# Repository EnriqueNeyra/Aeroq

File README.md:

# Aeroq

> [!IMPORTANT]
> **Aeroq is no longer maintained. Its successor is [Aether](https://github.com/EnriqueNeyra/aether).**
>
> Aether is the new version of this project. It uses a Sensirion SEN66 sensor (adding NOx), runs ESPHome firmware with Home Assistant integration, and adds a local web dashboard, OTA updates, and a browser-based USB flasher. For a new build, use Aether.
>
> This repository is kept as a reference for existing Aeroq v3 builds and will not receive further updates.

### A comprehensive indoor air quality monitor, capturing Temperature, Relative Humidity, CO2 (ppm), VOC (Index), and PM 1.0, 2.5, 4.0, 10 (ug/m3)

## Contents
- [Project Overview](#project-overview)
- [Required Hardware](#required-hardware)
- [Firmware Setup](#firmware-setup)
- [Assembly](#assembly)
- [Using Aeroq](#using-aeroq)
- [Troubleshooting](#troubleshooting)

---
## Project Overview

### Hardware
Schematic and PCB designed using KiCad. Schematic, PCB design, and manufacturing files can be found under [Aeroq Hardware/](./Aeroq%20Hardware/v3). The manufacturing package (Gerbers, drill files, and the PCBWay BOM, positions, and netlist) is `Aeroq Hardware/v3/Aeroq Hardware v3.kicad_pcb.zip`.

### Enclosure
Two 3D printed components are required for the assembly. Model files can be found under [Aeroq Enclosure/](./Aeroq%20Enclosure)

### Firmware
Source code for ESP32 firmware, developed with PlatformIO. Can be found under [Aeroq Firmware/](./Aeroq%20Firmware)

---

## Required Hardware  

| Item | Link |
|------|------|
| Custom PCB Order | [PCBWay](https://www.pcbway.com/project/shareproject/Air_Quality_Monitor_a6b051c5.html) |
| SEN54 (VOC/PM) Sensor | [Sensirion](https://sensirion.com/products/catalog/SEN54) |
| Enclosure 3D Print Files | [Printables](https://www.printables.com/model/1394330-indoor-air-quality-monitor) |
| 3.7" 240x416 E-Paper Display | [GoodDisplay](https://buyepaper.com/products/37-inch-416x240-e-paper-black-and-white-spi-fast-refresh-electronic-eink-display-screen-esl-gdey037t03) |
| JST GH 6 Pin Cable | [Adafruit](https://www.adafruit.com/product/5754#description) |

The SEN54 cable must connect pin 1 on the PCB to pin 1 on the SEN54. The board's connector uses the same pin order as the sensor (1: 5V, 2: GND, 3: SDA, 4: SCL, 5: GND, 6: NC). A cable that mirrors the pins leaves the sensor unpowered; see [Troubleshooting](#troubleshooting).

---

## Firmware Setup

This project uses [PlatformIO](https://platformio.org/), a plugin for VSCode that streamlines ESP32 development. The firmware is written in C++ and targets the **ESP32-C3** microcontroller.  

### Steps

1. **Install VSCode**  
   Download and install [Visual Studio Code](https://code.visualstudio.com/).

2. **Install PlatformIO**  
   In VSCode, open the Extensions tab (`Ctrl+Shift+X`), search for **PlatformIO IDE**, and install it.

3. **Clone this Repository**  
   ```bash
   git clone https://github.com/EnriqueNeyra/Aeroq.git
   cd "Aeroq/Aeroq Firmware"
   ```

4. **Open Project in PlatformIO**  
   - In VSCode, go to *File > Open Folder*  
   - Select the `Aeroq Firmware/` directory.  

5. **Connect the ESP32-C3**  
   - Use a USB-C cable to connect the board to your computer.  
   - Ensure the correct COM port/device is available  
   - PlatformIO detects the port automatically. If several boards are connected, set `upload_port` / `monitor_port` in platformio.ini  

6. **Build and Upload**  
   In PlatformIO, use the toolbar at the bottom:  
   - **Build**: Compile the firmware  
   - **Upload**: Flash firmware to the ESP32-C3  

7. **Monitor Serial Output (Optional)**  
   - Use the PlatformIO **Serial Monitor** to view sensor readings  
   - Default baud rate: `115200`

---

## Assembly

### 1. Components should connect as pictured below

### 2. Insert the SEN54 into the slot in the enclosure, ensuring it is pressed in all the way

### 3. Place display into frame

### 4. Orient the PCB so that it sits against the back of the display. This CAD assembly image illustrates the correct component orientation

### 5. Press the enclosure shut. The USB-C port should be visible and accessible through the slot at the rear

---

## Using Aeroq

Simply plug the device in using any USB-C cable/power supply (minimum 5V 1A), and wait for the initialization to complete.  
**For optimal measurement accuracy, keep it away from heat sources (electronics, lights, etc) and in an area with minimal clutter.**

---

## Troubleshooting

**Display shows "--" and "SEN54 not responding", or the serial monitor shows `[SEN54] readMeasuredValues() error = 270`**  
Error 270 means the SEN54 isn't answering on I2C. With the power unplugged, check that the cable connects PCB pin 1 to SEN54 pin 1. Then power the board and measure between SEN54 pin 1 and pin 2: the SEN54 needs at least 4.5V.

**Readings drop out or the board resets on some power supplies**  
The SEN54 runs from USB 5V after a protection diode, so it only gets about 4.5–4.7V. Use a 5V 1A adapter or a computer port directly, not a USB hub or a long, thin cable. Aether's hardware removes this limitation.

**Upload fails or the board doesn't show up as a serial port**  
Unplug the display and the SEN54, and connect the board directly to your computer rather than through a hub. Hold BOOT, press and release RESET, then release BOOT to enter download mode, and upload again. Reconnect the display and sensor afterwards.

## License

- **Firmware** (everything in [Aeroq Firmware/](./Aeroq%20Firmware)) is licensed under the [GNU General Public License v3.0](./Aeroq%20Firmware/LICENSE). It links the GPL-3.0 GxEPD2 display library.
- **Hardware and enclosure** (schematic, PCB, CAD, and other design files) are licensed under the [Creative Commons Attribution-NonCommercial-ShareAlike 4.0 International License](http://creativecommons.org/licenses/by-nc-sa/4.0/). See [LICENSE](./LICENSE).

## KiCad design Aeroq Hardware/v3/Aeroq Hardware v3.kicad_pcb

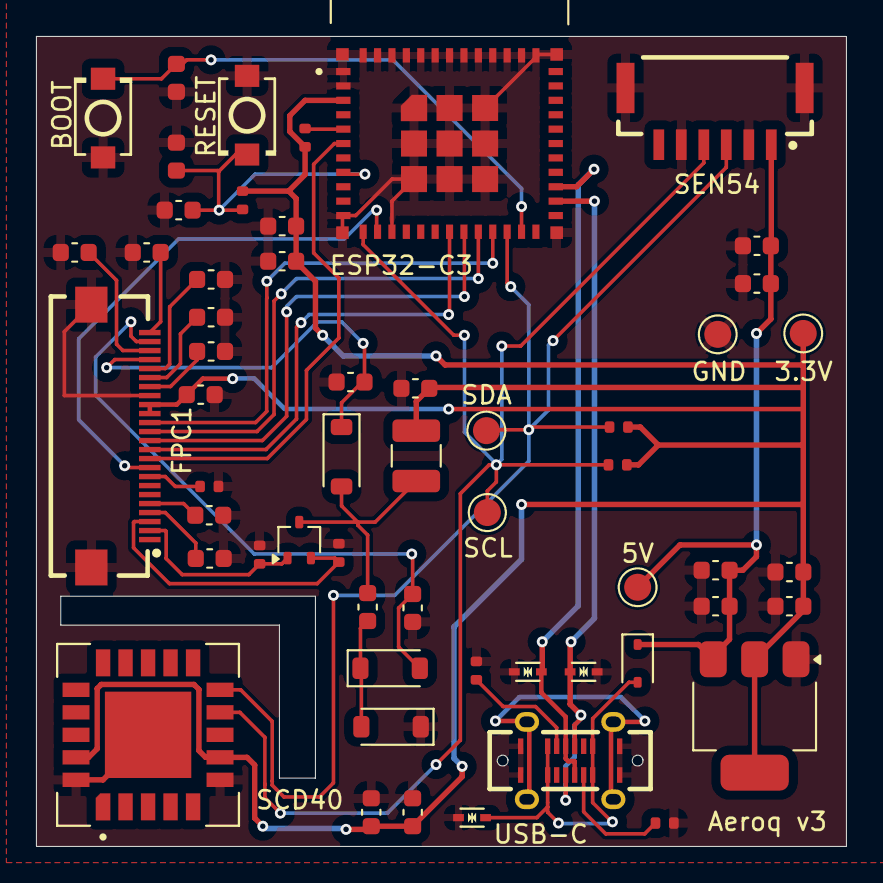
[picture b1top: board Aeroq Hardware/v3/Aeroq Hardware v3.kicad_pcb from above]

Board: 2 copper layers, 45.0 x 45.0 mm, 56 parts (0 on the bottom side), 33 nets.

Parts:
C1, C6, C9: 10uf/25V; C_0603_1608Metric
C2, C3, C5, C7, C8, C11, C15: 0.1uf/50V; C_0603_1608Metric
C4, C20, C21, C22, C25: 1uf/50V; C_0603_1608Metric
C10, C12, C13, C14, C16, C17, C18, C19, C23, C24: 4.7uf/25V; C_0603_1608Metric
D1: 1N5819WS; D_SOD-323
D2, D3, D4: SOD-523_L1.2-W0.8-LS1.6-BI
D5, D6, D7: MBR0530; D_SOD-123
FPC1: FPC-SMD_24P-P0.50_FPC-05FB-24PH20
L1: 10uH/1A; L_1210_3225Metric
Q1: Si1308EDL; SOT-323_SC-70
R1, R2, R5, R6, R9: 10k; R_0402_1005Metric
R3, R4: 5k; R_0402_1005Metric
R7: 3; R_0402_1005Metric
R10: 0.47; R_0402_1005Metric
SW1, SW2: SW-SMD_L3.9-W3.0-P4.45
TP1, TP2, TP3, TP4, TP5: TestPoint; TestPoint_Pad_D1.5mm
U1: TYPE-C-SMD_USB4120-03-C
U2: ESP32-C3-MINI-1-N4; XCVR_ESP32-C3-MINI-1-N4
U3: AMS1117-3.3; SOT-223-3_TabPin2
U4: SCD40-D-R1; XDCR_SCD40-D-R1
U5: CONN-SMD_6P-P1.25_XUNPU_WAFER-GH1.25-6PWB

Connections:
+3.3V: C1.2, C2.1, C8.1, C9.2, C15.1, C16.2, C18.1, C20.2, FPC1.15, FPC1.16, L1.1, R1.2, R2.2, R5.2, R6.2, TP2.1, U2.3 (3V3), U3.2 (VO), U4.7 (VDD), U4.19 (VDDH)
+5V: C6.2, C7.1, C10.2, C11.1, D1.1 (K), TP3.1, U3.3 (VI), U5.1
BUSY: FPC1.9, U2.13 (IO1)
CHIP_PU: C4.2, C5.1, R1.1, SW2.2, U2.8 (EN)
CS: FPC1.12, U2.19 (IO5)
D+: D4.2, U1.A6 (DP1), U1.B6 (DP2), U2.27 (IO19)
D-: D3.2, U1.A7 (DN1), U1.B7 (DN2), U2.26 (IO18)
DC: FPC1.11, U2.18 (IO4)
GDR: FPC1.2, Q1.1 (G), R9.2
GND: C1.1, C2.2, C3.2, C4.1, C5.2, C6.1, C7.2, C8.2, C9.1, C10.1, C11.2, C12.1, C13.2, C14.1, C15.2, C16.1, C18.2, C19.2, C20.1, C21.2, C22.2, C23.1, C24.1, C25.1, D2.1, D3.1, D4.1, D6.1 (K), FPC1.17, FPC1.25, FPC1.26, R3.1, R4.1, R7.2, R9.1, R10.1, SW1.1, SW2.1, TP1.1, U1.A1 (GND), U1.A12 (GND), U1.B1 (GND), U1.B12 (GND), U2.1 (GND), U2.2 (GND), U2.11 (GND), U2.14 (GND), U2.36 (GND), U2.37 (GND), U2.38 (GND), U2.39 (GND), U2.40 (GND), U2.41 (GND), U2.42 (GND), U2.43 (GND), U2.44 (GND), U2.45 (GND), U2.46 (GND), U2.47 (GND), U2.48 (GND), U2.49_1 (GND), U2.49_2 (GND), U2.49_3 (GND), U2.49_4 (GND), U2.49_5 (GND), U2.49_6 (GND), U2.49_7 (GND), U2.49_8 (GND), U2.49_9 (GND), U2.50 (GND), U2.51 (GND), U2.52 (GND), U2.53 (GND), U3.1 (GND), U4.6 (GND), U4.20 (GND), U4.21 (GND), U5.2, U5.5, U5.7, U5.8
GPIO2: R2.1, U2.5 (IO2)
GPIO9: C3.1, SW1.2, U2.23 (IO9)
unnamed: C12.2, FPC1.4
unnamed: C14.2, FPC1.5
unnamed: C21.1, FPC1.18
unnamed: C22.1, FPC1.19
unnamed: C23.2, FPC1.20
unnamed: C24.2, FPC1.22
unnamed: C25.2, FPC1.24
unnamed: C17.1, D5.1 (K), D6.2 (A)
unnamed: C17.2, D7.2 (A), L1.2, Q1.3 (D)
unnamed: FPC1.8, R7.1
unnamed: R4.2, U1.A5 (CC1)
unnamed: R3.2, U1.B5 (CC2)
PREVGH: C19.1, D7.1 (K), FPC1.21
PREVGL: C13.1, D5.2 (A), FPC1.23
RES: FPC1.10, U2.6 (IO3)
RESE: FPC1.3, Q1.2 (S), R10.2
SCL: R5.1, TP4.1, U2.12 (IO0), U4.9 (SCL), U5.4
SCLK: FPC1.13, U2.20 (IO6)
SDA: R6.1, TP5.1, U2.22 (IO8), U4.10 (SDA), U5.3
SDI: FPC1.14, U2.21 (IO7)
VBUS: D1.2 (A), D2.2, U1.A4 (VBUS), U1.A9 (VBUS), U1.B4 (VBUS), U1.B9 (VBUS)

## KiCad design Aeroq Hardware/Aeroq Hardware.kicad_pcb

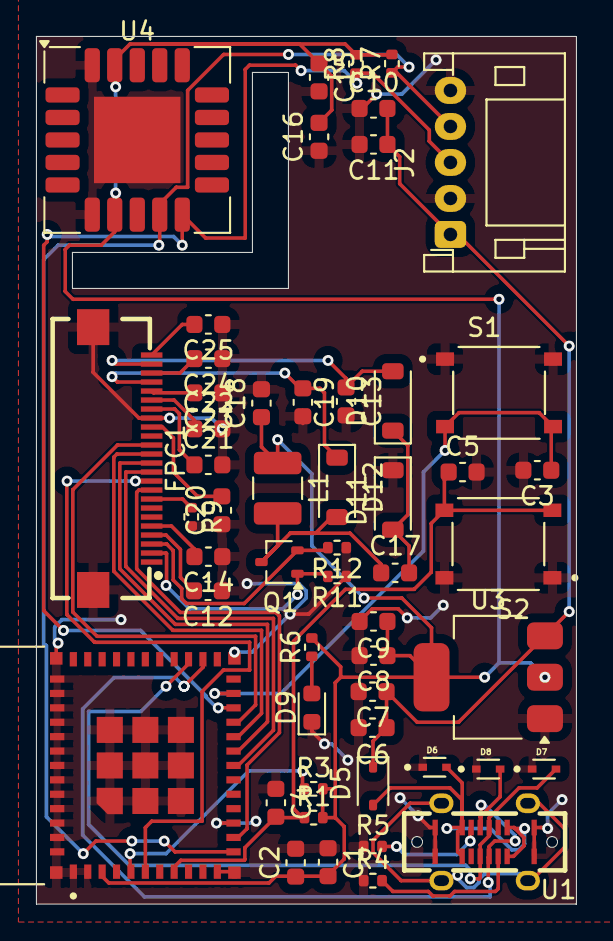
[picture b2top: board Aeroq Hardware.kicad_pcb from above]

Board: 2 copper layers, 30.0 x 48.2 mm, 53 parts (0 on the bottom side), 35 nets.

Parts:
C1, C6, C9: 10uf/25V; C_0603_1608Metric
C2, C3, C5, C7, C8, C11, C15: 0.1uf/50V; C_0603_1608Metric
C4, C20, C21, C22, C25: 1uf/50V; C_0603_1608Metric
C10, C12, C13, C14, C16, C17, C18, C19, C23, C24: 4.7uf/25V; C_0603_1608Metric
D5: 1N5819WS; D_SOD-323
D6, D7, D8: LESD5D5.0CT1G; TVS_LESD5D5.0CT1G
D9: LED; LED_0603_1608Metric
D10, D11, D12: MBR0530; D_SOD-123
FPC1: FPC-SMD_24P-P0.50_FPC-05FB-24PH20
J2: Conn_01x05; JST_PH_S5B-PH-K_1x05_P2.00mm_Horizontal
L1: 10uH/1A; L_1210_3225Metric
Q1: Si1308EDL; SOT-323_SC-70
R1, R3, R6, R7, R8, R11: 10kR; R_0402_1005Metric
R4, R5: 5kR; R_0402_1005Metric
R9: 3R; R_0402_1005Metric
R12: 0.47R; R_0402_1005Metric
S1, S2: TS-1187A-B-A-B; SW_TS-1187A-B-A-B
U1: TYPE-C-SMD_USB4120-03-C
U2: ESP32-C3-MINI-1-N4; XCVR_ESP32-C3-MINI-1-N4
U3: AMS1117-3.3; SOT-223-3_TabPin2
U4: SCD40-D-R1; Sensirion_SCD4x-1EP_10.1x10.1mm_P1.25mm_EP4.8x4.8mm

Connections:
+3.3V: C1.2, C2.1, C8.1, C9.2, C15.1, C16.2, C18.1, L1.1, R1.2, R3.2, R6.2, R7.2, R8.2, U2.3 (3V3), U3.2 (VO), U4.7 (VDD), U4.19 (VDDH)
+5V: C6.2, C7.1, C10.2, C11.1, D5.1 (K), J2.1, U3.3 (VI)
BUSY: FPC1.9, U2.13 (IO1)
CHIP_PU: C4.2, C5.1, R1.1, S2.C, S2.D, U2.8 (EN)
CS: FPC1.12, U2.19 (IO5)
D+: D8.2, U1.A6 (DP1), U1.B6 (DP2), U2.26 (IO18)
D-: D7.2, U1.A7 (DN1), U1.B7 (DN2), U2.27 (IO19)
DC: FPC1.11, U2.18 (IO4)
GDR: FPC1.2, Q1.1 (G), R11.2
GND: C1.1, C2.2, C3.2, C4.1, C5.2, C6.1, C7.2, C8.2, C9.1, C10.1, C11.2, C12.1, C13.2, C14.1, C15.2, C16.1, C18.2, C19.2, C20.1, C21.2, C22.2, C23.1, C24.1, C25.1, D6.1, D7.1, D8.1, D9.1 (K), D11.1 (K), FPC1.17, FPC1.25, FPC1.26, J2.2, J2.5, R4.1, R5.1, R9.2, R11.1, R12.1, S1.A, S1.B, S2.A, S2.B, U1.A1 (GND), U1.A12 (GND), U1.B1 (GND), U1.B12 (GND), U2.1 (GND), U2.2 (GND), U2.11 (GND), U2.14 (GND), U2.36 (GND), U2.37 (GND), U2.38 (GND), U2.39 (GND), U2.40 (GND), U2.41 (GND), U2.42 (GND), U2.43 (GND), U2.44 (GND), U2.45 (GND), U2.46 (GND), U2.47 (GND), U2.48 (GND), U2.49_1 (GND), U2.49_2 (GND), U2.49_3 (GND), U2.49_4 (GND), U2.49_5 (GND), U2.49_6 (GND), U2.49_7 (GND), U2.49_8 (GND), U2.49_9 (GND), U2.50 (GND), U2.51 (GND), U2.52 (GND), U2.53 (GND), U3.1 (GND), U4.6 (GND), U4.20 (GND), U4.21 (GND)
GPIO2: R3.1, U2.5 (IO2)
GPIO9: C3.1, S1.C, S1.D, U2.23 (IO9)
unnamed: C12.2, FPC1.4
unnamed: C14.2, FPC1.5
unnamed: C20.2, FPC1.16
unnamed: C21.1, FPC1.18
unnamed: C22.1, FPC1.19
unnamed: C23.2, FPC1.20
unnamed: C24.2, FPC1.22
unnamed: C25.2, FPC1.24
unnamed: D9.2 (A), R6.1
unnamed: C17.1, D10.1 (K), D11.2 (A)
unnamed: C17.2, D12.2 (A), L1.2, Q1.3 (D)
unnamed: FPC1.8, R9.1
unnamed: R5.2, U1.A5 (CC1)
unnamed: R4.2, U1.B5 (CC2)
PREVGH: C19.1, D12.1 (K), FPC1.21
PREVGL: C13.1, D10.2 (A), FPC1.23
RES: FPC1.10, U2.6 (IO3)
RESE: FPC1.3, Q1.2 (S), R12.2
SCL: J2.4, R7.1, U2.12 (IO0), U4.9 (SCL)
SCLK: FPC1.13, U2.20 (IO6)
SDA: J2.3, R8.1, U2.22 (IO8), U4.10 (SDA)
SDI: FPC1.14, U2.21 (IO7)
VBUS: D5.2 (A), D6.2, U1.A4 (VBUS), U1.A9 (VBUS), U1.B4 (VBUS), U1.B9 (VBUS)

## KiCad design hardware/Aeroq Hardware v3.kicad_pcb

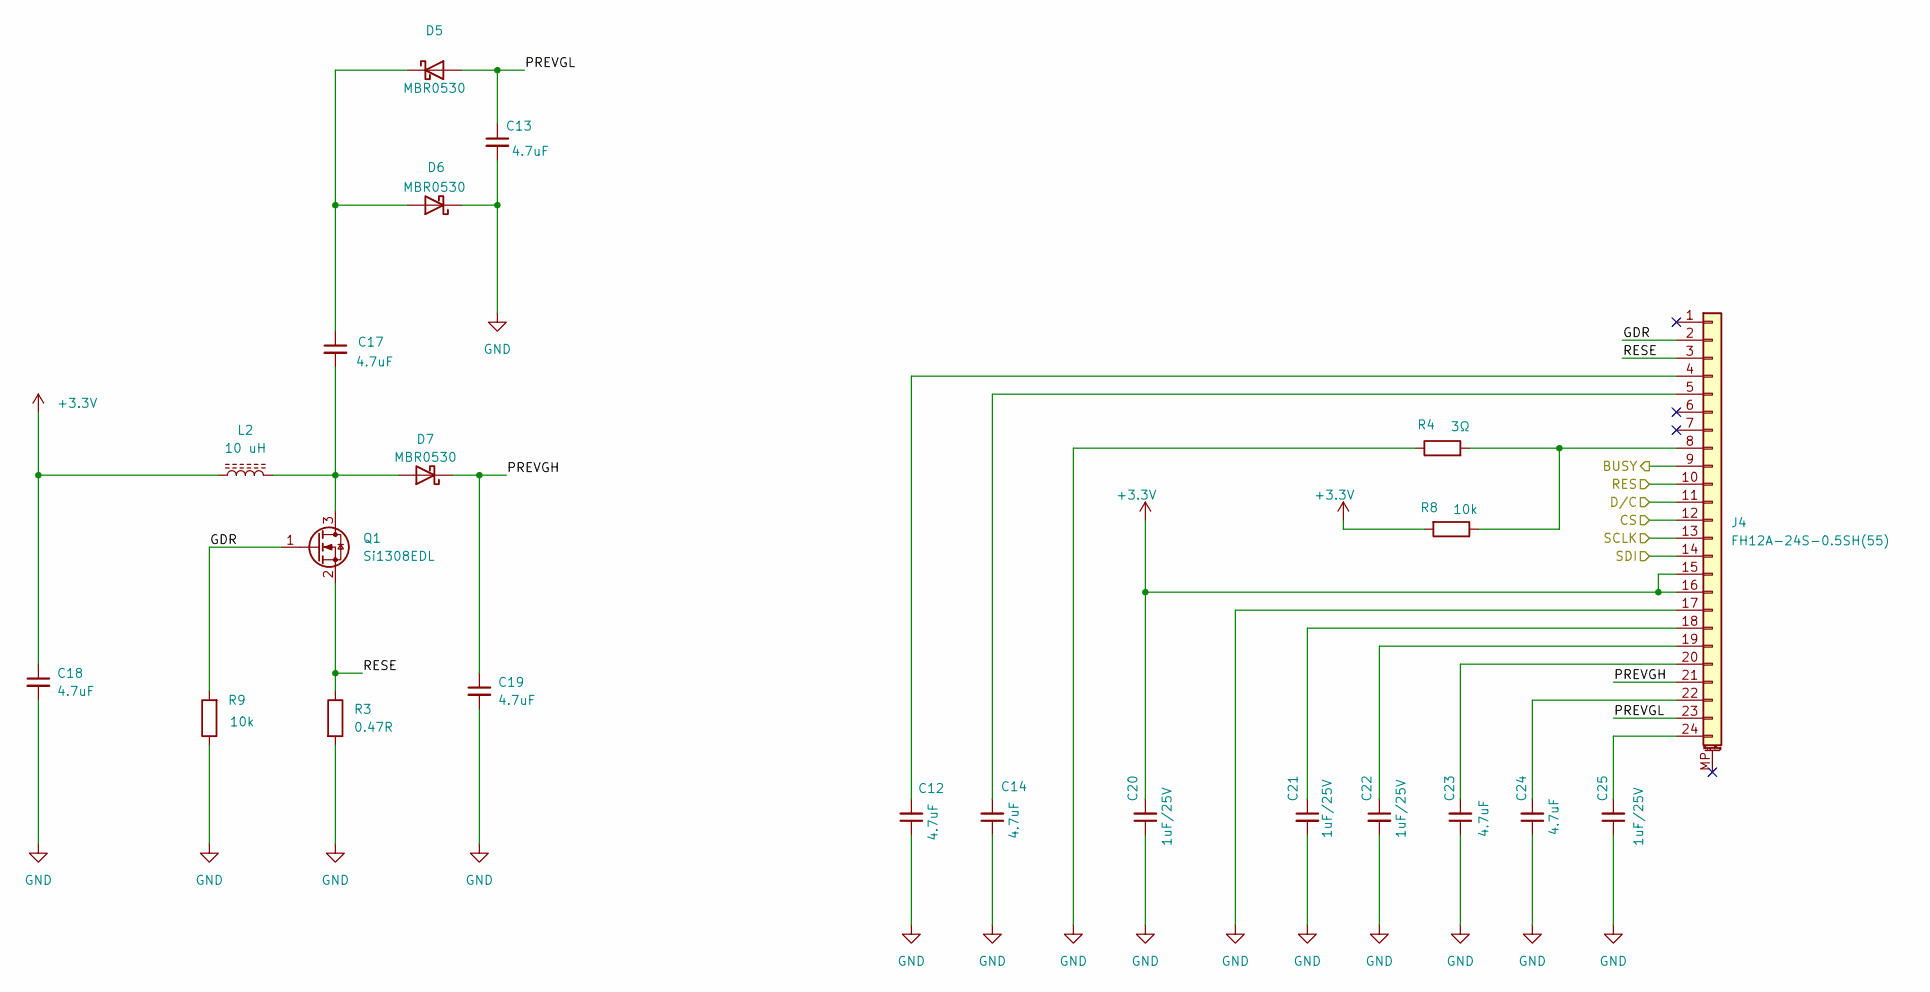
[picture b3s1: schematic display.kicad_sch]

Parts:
C12, C13, C14, C17, C18, C19, C23, C24: 4.7uF_0603_25V; C_0603_1608Metric; MPN GRM188R61E475KE11D
C20, C21, C22, C25: 1uF_0603_25V; C_0603_1608Metric; MPN GRM188R61E105KA12D; JLCPCB ID C15849
D5, D6, D7: MBR0530; D_SOD-123; MPN MBR0530-TP; Digi-Key_PN MBR0530TPMSTR-ND
J4: FH12A-24S-0.5SH(55); Hirose_FH12-24S-0.5SH_1x24-1MP_P0.50mm_Horizontal_INVERTED; MPN FH12A-24S-0.5SH(55); Digi-Key_PN HFK124CT-ND
L2: 10 uH; L_Wuerth_MAPI-3020; MPN 7447732110; Digi-Key_PN 732-11499-2-ND
Q1: Si1308EDL; SOT-323_SC-70; MPN SI1308EDL-T1-GE3; Digi-Key_PN SI1308EDL-T1-GE3TR-ND
R3: 0.47R_0603; R_0603_1608Metric; MPN ERJ-3RQFR47V; Digi-Key_PN P.47AJTR-ND
R4: 3Ω_0603; R_0603_1608Metric; MPN RC0603FR-073RL; JLCPCB ID C137724
R8, R9: 10k_0603; R_0603_1608Metric; MPN RC0603FR-0710KL; JLCPCB ID C98220

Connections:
+3.3V: C18.1, C20.2, J4.15, J4.16, L2.1, R8.2; also elsewhere on the board
/Display/BUSY: J4.9; also elsewhere on the board
/Display/CS: J4.12; also elsewhere on the board
/Display/D/C: J4.11; also elsewhere on the board
/Display/GDR: J4.2, Q1.1 (G), R9.2
/Display/PREVGH: C19.1, D7.1 (K), J4.21
/Display/PREVGL: C13.1, D5.2 (A), J4.23
/Display/RES: J4.10; also elsewhere on the board
/Display/RESE: J4.3, Q1.2 (S), R3.1
/Display/SCLK: J4.13; also elsewhere on the board
/Display/SDI: J4.14; also elsewhere on the board
GND: C12.1, C13.2, C14.1, C18.2, C19.2, C20.1, C21.2, C22.2, C23.1, C24.1, C25.1, D6.1 (K), J4.17, R3.2, R4.1, R9.1; also elsewhere on the board
unnamed: C17.1, D5.1 (K), D6.2 (A)
unnamed: C17.2, D7.2 (A), L2.2, Q1.3 (D)
unnamed: C12.2, J4.4
unnamed: C14.2, J4.5
unnamed: J4.8, R4.2, R8.1
unnamed: C21.1, J4.18
unnamed: C22.1, J4.19
unnamed: C23.2, J4.20
unnamed: C24.2, J4.22
unnamed: C25.2, J4.24

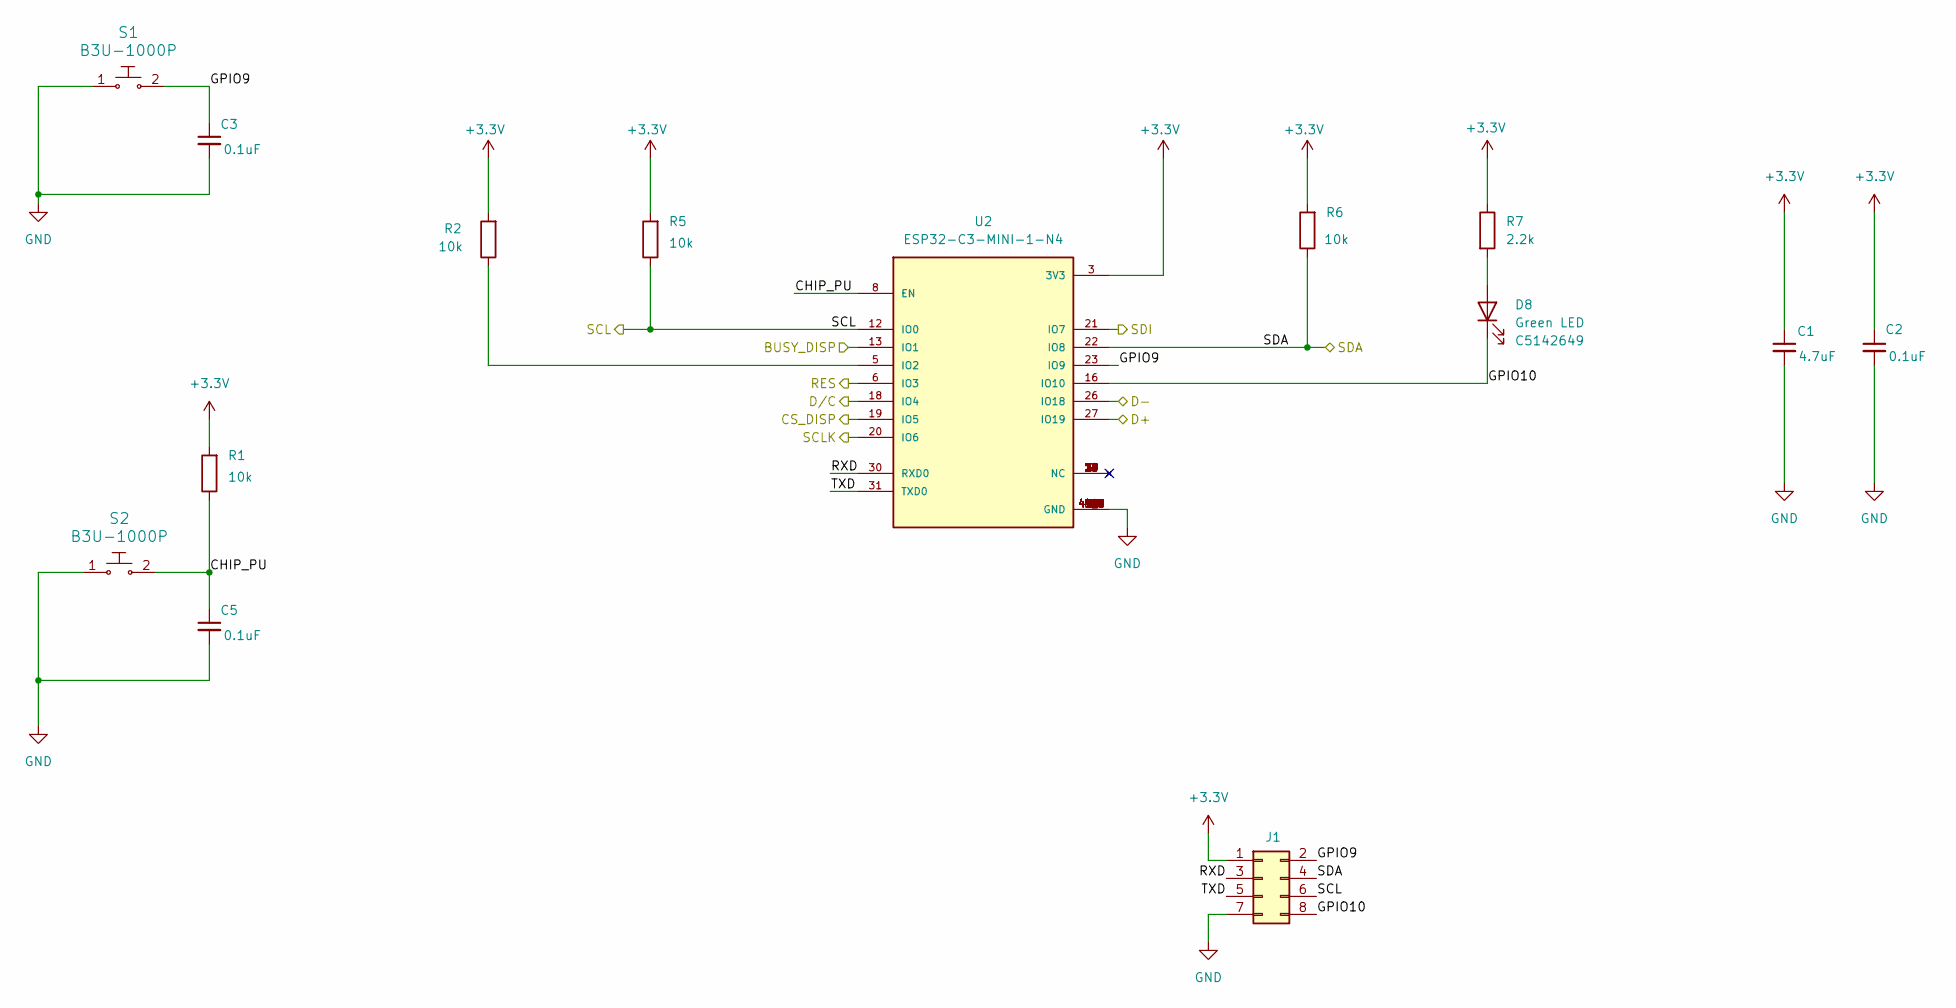
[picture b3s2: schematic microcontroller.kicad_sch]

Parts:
C1: 4.7uF_0603_25V; C_0603_1608Metric; MPN GRM188R61E475KE11D
C2, C3, C5: 100nF_0603_16V; C_0603_1608Metric; MPN 0603YC104KAT2A; JLCPCB ID C14663
D8: Green LED; LED_1206_3216Metric; MPN 150120GS75000; Digi-Key_PN 732-4990-1-ND
J1: 2x4 male header 2.54 mm; PinHeader_2x04_P2.54mm_Vertical_SMD; MPN 54202-G0804LF; Digi-Key_PN 609-54202-G0804LF-ND
R1, R2, R5, R6: 10k_0603; R_0603_1608Metric; MPN RC0603FR-0710KL; JLCPCB ID C98220
R7: 2.2k_0603; R_0603_1608Metric; MPN RC0603FR-072K2L; JLCPCB ID C114662
S1, S2: B3U-1000P; SW_SPST_B3U-1000P; MPN B3U-1000P; Digi-Key_PN SW1020TR-ND
U2: ESP32-C3-MINI-1-N4; XCVR_ESP32-C3-MINI-1-N4; MPN ESP32-C3-MINI-1-N4; Digi-Key_PN 5407-ESP32-C3-MINI-1-N4CT-ND

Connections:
+3.3V: C1.1, C2.1, J1.1, R1.2, R2.2, R5.2, R6.2, R7.1, U2.3 (3V3); also elsewhere on the board
/Display/BUSY: U2.13 (IO1); also elsewhere on the board
/Display/CS: U2.19 (IO5); also elsewhere on the board
/Display/D/C: U2.18 (IO4); also elsewhere on the board
/Display/RES: U2.6 (IO3); also elsewhere on the board
/Display/SCLK: U2.20 (IO6); also elsewhere on the board
/Display/SDI: U2.21 (IO7); also elsewhere on the board
/Microcontroller/CHIP_PU: C5.1, R1.1, S2.2, U2.8 (EN)
/Microcontroller/GPIO9: C3.1, J1.2, S1.2, U2.23 (IO9)
/Microcontroller/GPIO10: D8.1 (K), J1.8, U2.16 (IO10)
/Microcontroller/RXD: J1.3, U2.30 (RXD0)
/Microcontroller/SCL: J1.6, R5.1, U2.12 (IO0); also elsewhere on the board
/Microcontroller/SDA: J1.4, R6.1, U2.22 (IO8); also elsewhere on the board
/Microcontroller/TXD: J1.5, U2.31 (TXD0)
/USB-C/D+: U2.27 (IO19); also elsewhere on the board
/USB-C/D-: U2.26 (IO18); also elsewhere on the board
GND: C1.2, C2.2, C3.2, C5.2, J1.7, S1.1, S2.1, U2.1 (GND), U2.2 (GND), U2.11 (GND), U2.14 (GND), U2.36 (GND), U2.37 (GND), U2.38 (GND), U2.39 (GND), U2.40 (GND), U2.41 (GND), U2.42 (GND), U2.43 (GND), U2.44 (GND), U2.45 (GND), U2.46 (GND), U2.47 (GND), U2.48 (GND), U2.49_1 (GND), U2.49_2 (GND), U2.49_3 (GND), U2.49_4 (GND), U2.49_5 (GND), U2.49_6 (GND), U2.49_7 (GND), U2.49_8 (GND), U2.49_9 (GND), U2.50 (GND), U2.51 (GND), U2.52 (GND), U2.53 (GND); also elsewhere on the board
unnamed: D8.2 (A), R7.2
unnamed: R2.1, U2.5 (IO2)

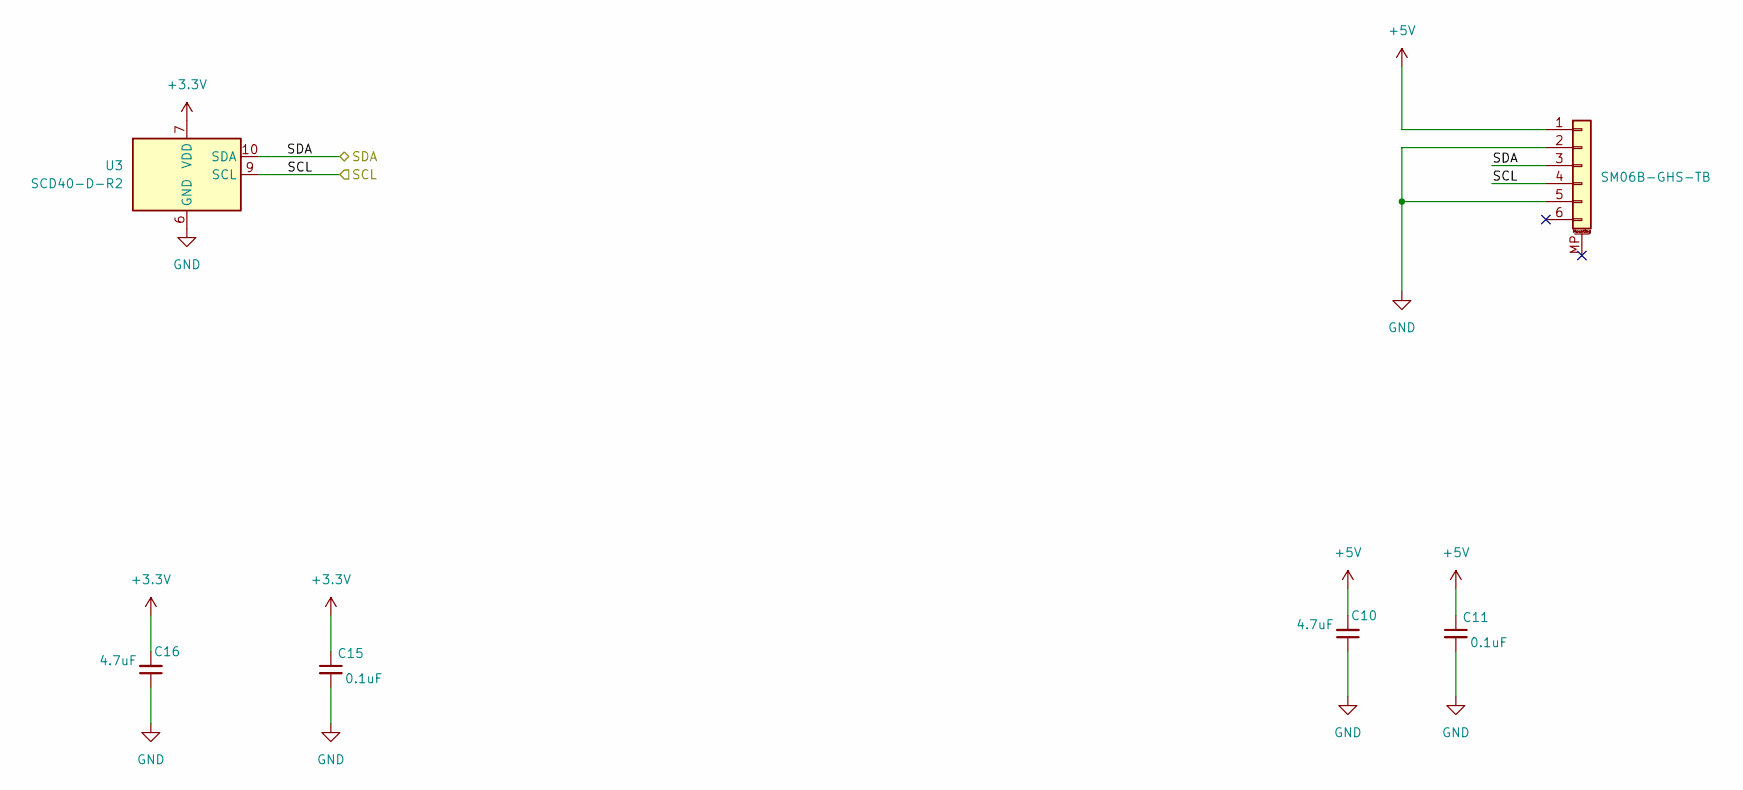
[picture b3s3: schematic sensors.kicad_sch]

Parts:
C10, C16: 4.7uF_0603_25V; C_0603_1608Metric; MPN GRM188R61E475KE11D
C11, C15: 100nF_0603_16V; C_0603_1608Metric; MPN 0603YC104KAT2A; JLCPCB ID C14663
J3: SM06B-GHS-TB; JST_GH_SM06B-GHS-TB_1x06-1MP_P1.25mm_Horizontal; MPN SM06B-GHS-TB; Digi-Key_PN 455-1568-1-ND
U3: SCD40-D-R2; Sensirion_SCD4x-1EP_10.1x10.1mm_P1.25mm_EP4.8x4.8mm; MPN SCD40-D-R2; Digi-Key_PN 1649-SCD40-D-R2TR-ND

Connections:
+3.3V: C15.1, C16.2, U3.7 (VDD), U3.19 (VDD); also elsewhere on the board
+5V: C10.2, C11.1, J3.1; also elsewhere on the board
/Microcontroller/SCL: J3.4, U3.9 (SCL); also elsewhere on the board
/Microcontroller/SDA: J3.3, U3.10 (SDA); also elsewhere on the board
GND: C10.1, C11.2, C15.2, C16.1, J3.2, J3.5, U3.6 (GND), U3.20 (GND), U3.21 (GND); also elsewhere on the board

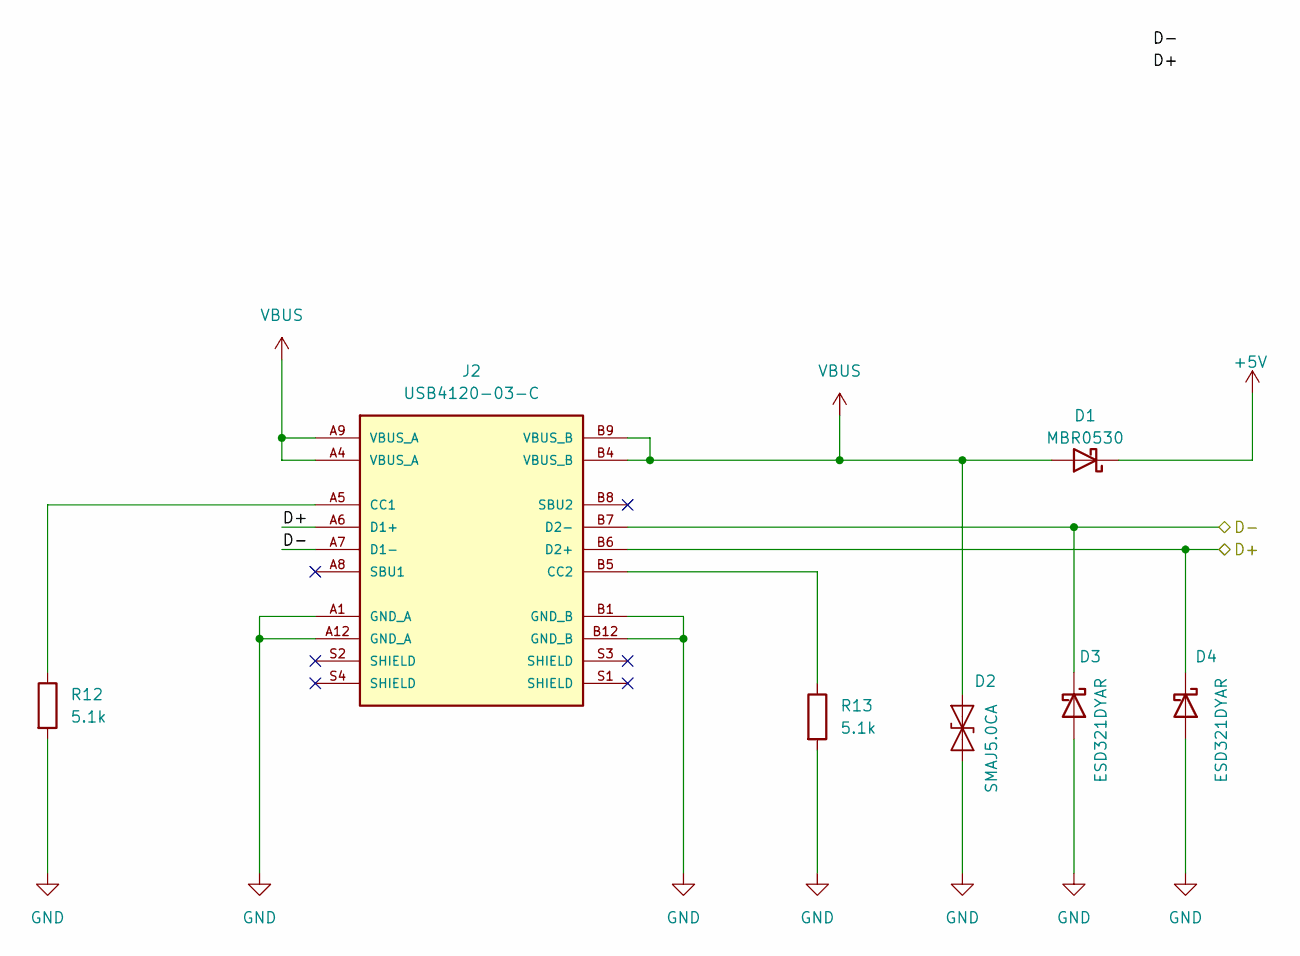
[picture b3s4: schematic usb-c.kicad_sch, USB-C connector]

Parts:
D1: MBR0530; D_SOD-123; MPN MBR0530-TP; Digi-Key_PN MBR0530TPMSTR-ND
D2: SMAJ5.0CA; D_SMA; MPN SMAJ5.0CA; Digi-Key_PN SMAJ5.0CALFTR-ND
D3, D4: ESD321DYAR; SOT-523; MPN ESD321DYAR; Digi-Key_PN 296-ESD321DYARTR-ND
J2: USB4120-03-C; GCT_USB4120-03-C_REVA; MPN USB4120-03-C; Digi-Key_PN 2073-USB4120-03-CTR-ND
R12, R13: 5.1k_0603; R_0603_1608Metric; MPN RC0603FR-075K1L; JLCPCB ID C105580

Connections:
+5V: D1.1 (K); also elsewhere on the board
/USB-C/D+: D4.1 (K), J2.A6 (D1+), J2.B6 (D2+); also elsewhere on the board
/USB-C/D-: D3.1 (K), J2.A7 (D1-), J2.B7 (D2-); also elsewhere on the board
GND: D2.1 (A1), D3.2 (A), D4.2 (A), J2.A1 (GND_A), J2.A12 (GND_A), J2.B1 (GND_B), J2.B12 (GND_B), R12.2, R13.2; also elsewhere on the board
unnamed: J2.A5 (CC1), R12.1
unnamed: J2.B5 (CC2), R13.1
VBUS: D1.2 (A), D2.2 (A2), J2.A4 (VBUS_A), J2.A9 (VBUS_A), J2.B4 (VBUS_B), J2.B9 (VBUS_B)

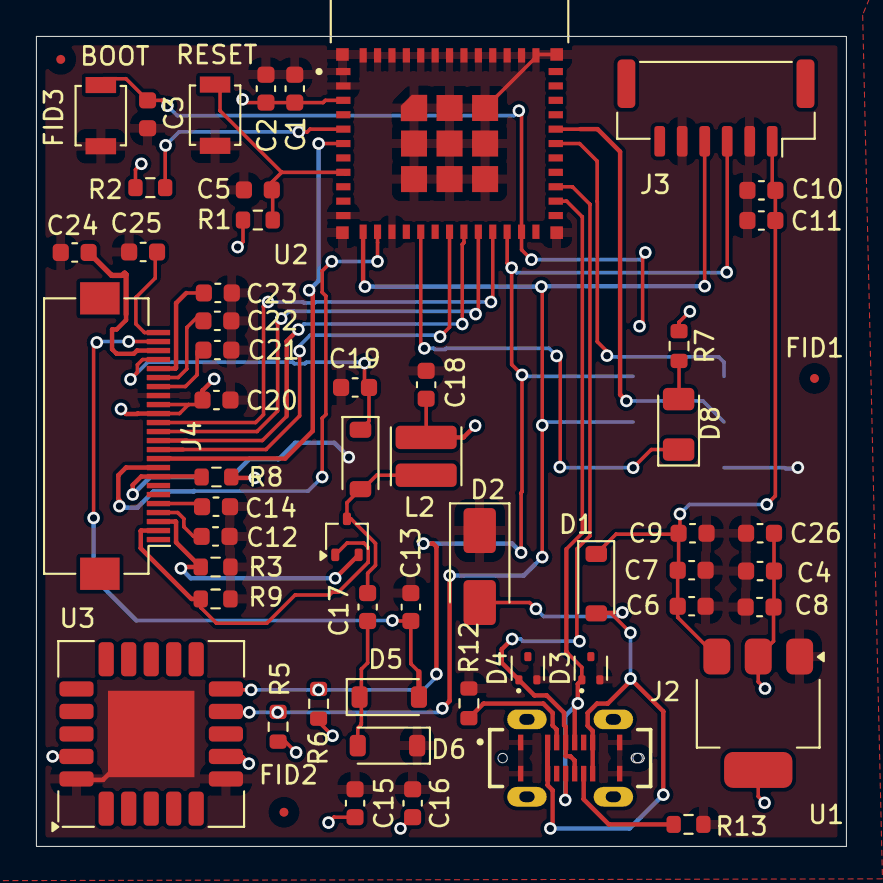
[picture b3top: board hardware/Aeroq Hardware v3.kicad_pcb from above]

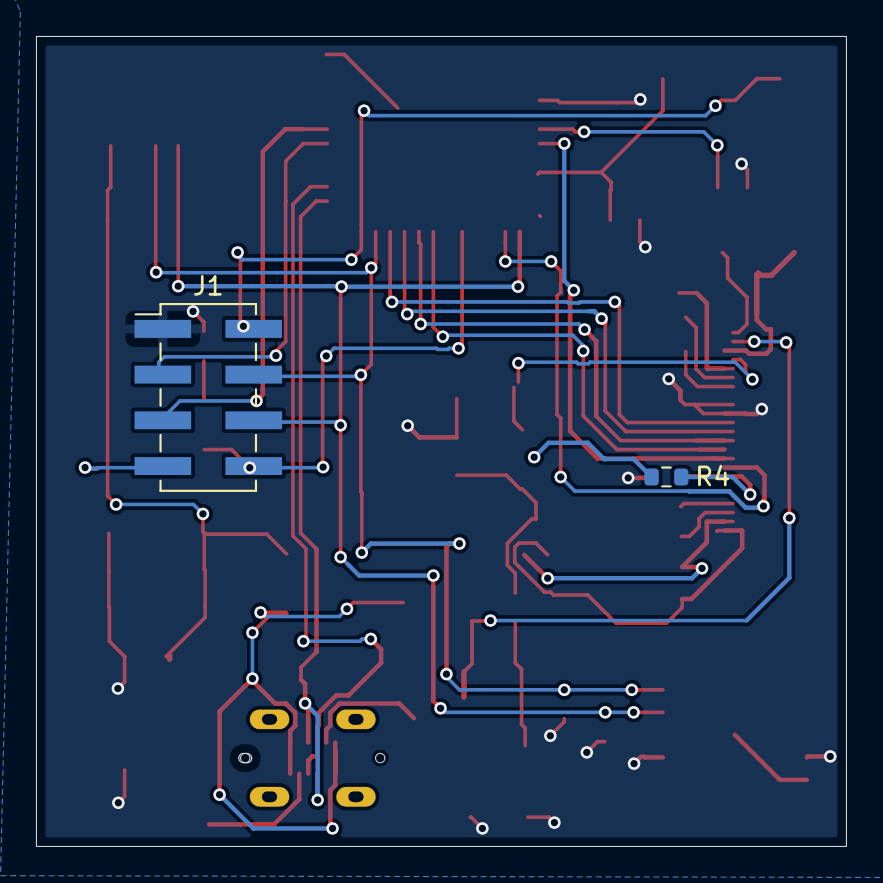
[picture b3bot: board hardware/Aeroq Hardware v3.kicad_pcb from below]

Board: 2 copper layers, 45.0 x 45.0 mm, 59 parts (2 on the bottom side), 37 nets.

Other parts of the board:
C4, C6, C9, C26: 4.7uF_0603_25V; C_0603_1608Metric
C7, C8: 100nF_0603_16V; C_0603_1608Metric
FID1, FID2, FID3: Fiducial; Fiducial_0.5mm_Mask1.5mm
U1: TLV76133DCY; SOT-223-3_TabPin2

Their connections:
+3.3V: C4.2, C8.1, C26.2, U1.2 (VO); also elsewhere on the board
+5V: C6.2, C7.1, C9.2, U1.3 (VI); also elsewhere on the board
GND: C4.1, C6.1, C7.2, C8.2, C9.1, C26.1, U1.1 (GND); also elsewhere on the board

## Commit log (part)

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2025-06-09 Initial KiCad Files
2025-06-18 schematic and pcb initial
2025-06-27 add v2 PCB, add initial software files
2025-07-23 Refactor ESP32-S3 Air Quality Monitor Code
    - Added lock files for PCB and schematic to track changes.
    - Updated platformio.ini to comment out the previous environment configuration and set up a new environment for esp32-c3-devkitm-1.
    - Modified main.cpp to enhance display functionality, including improved font sizes and layout for sensor readings.
    - Cleaned up commented-out code and organized the structure for better readability.
    - Implemented a more structured display update cycle with clear separation of sensor data.
    - Removed redundant code and improved comments for clarity.
2025-07-23 Add display refresh in setup
2025-08-10 Remove lock files and update platformio.ini and main.cpp for ESP32-S3 project
    - Deleted lock files for KiCad PCB and schematic to clean up project directory.
    - Changed monitor port from COM3 to COM4 in platformio.ini for correct serial communication.
    - Modified Serial initialization in main.cpp to include a timeout for better reliability during setup.
2025-08-10 Remove unused main2.cpp
2025-08-10 Move firmware folder
2025-08-11 Reorganize files, rename folders
2025-08-11 Remove outdated PCB versions
2025-08-24 updates to kicad schematic/pcb
2025-08-24 update test main2
2025-08-24 remove unused main2.cpp file and related code
2025-08-24 PCB Updates
2025-08-24 Create LICENSE
2025-08-27 Add original solidworks CAD files and assembly
2025-08-27 Add schematic+pcb pdf files for easier viewing
2025-09-01 KiCad schematic and PCB updates
2025-09-01 Add updated schematic/pcb PDFs
2025-09-02 Testing AWS IoT integration with telemetry publishing and connection management
2025-09-04 Refactor AWS IoT integration: remove old implementation and replace with new connection and message handling logic
2025-10-16 add my customizations
2025-10-16 remove generated documents
2025-10-16 renaming
2025-10-16 remove v3 folder
2025-10-16 remove backups
2025-10-16 remove BOM
2025-10-16 remove bak file
2025-11-05 add hardware backup
2025-11-05 prep for esphome integration
2025-11-10 ESPHome + HA initial integrations
2025-11-10 change folder structure for gh pages
2025-11-11 Updated github pages
2025-11-11 firmware updates and mockup actions pipeline
2025-11-12 esphome yaml updates to include webserver and updated gh pages flasher
2025-11-12 unfinished changes for custom web server
2025-11-12 updates to support custom web server
2025-11-13 move .gitignore
2025-11-13 implement custom web UI
2025-11-13 updated firmware
2025-11-14 yaml and gh pages updates
2025-11-16 general updates
2025-11-19 updated firmware testing
2025-11-22 OTA update and webserver updates
2025-11-22 update versions in manifest
2025-11-22 manifest update
